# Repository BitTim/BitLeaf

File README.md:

# BitLeaf
Hardware of my Nanoleaf clone and Firmware and App to control it.

## What is where?
All the firmware code for the Arduino and Attinys can be found in the arduino folder
All the schematics and PCB designs can be found in the pcbs folder

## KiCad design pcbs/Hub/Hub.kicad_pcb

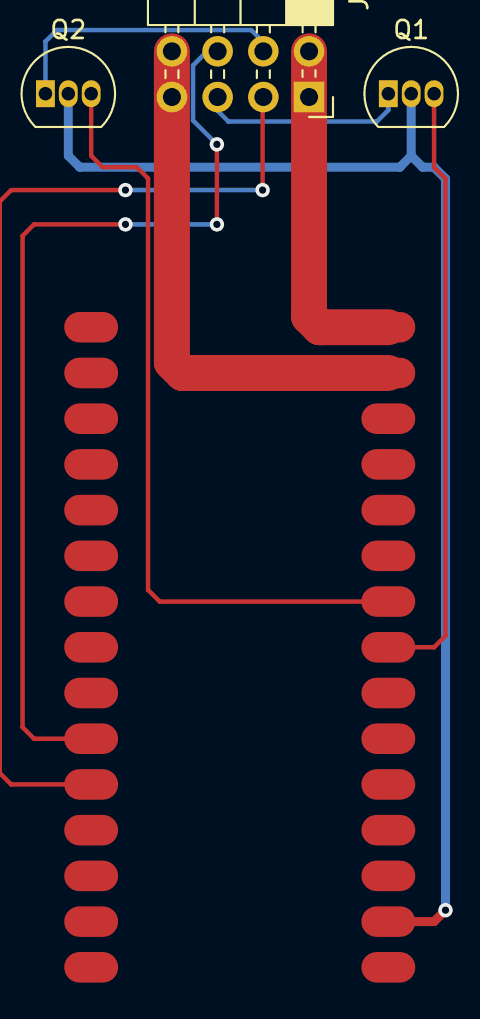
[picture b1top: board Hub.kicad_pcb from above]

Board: 2 copper layers, 4 parts (0 on the bottom side), 9 nets.

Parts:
J1: Arduino-NANO-33; NANO_33_Footprint_SMD_Castell
J2: Conn_A; PinSocket_2x04_P2.54mm_Horizontal
Q1, Q2: BS170; TO-92_Inline

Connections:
+3V3: J1.2, Q1.2 (G), Q2.2 (G)
+5V: J1.15, J2.1, J2.2
CONA: J1.26, J2.3
GND: J1.14, J2.7, J2.8
RDYA: J1.25, J2.6
SCL_3V3: J1.9, Q2.3 (S)
SCL_5V: J2.4, Q2.1 (D)
SDA_3V3: J1.8, Q1.3 (S)
SDA_5V: J2.5, Q1.1 (D)

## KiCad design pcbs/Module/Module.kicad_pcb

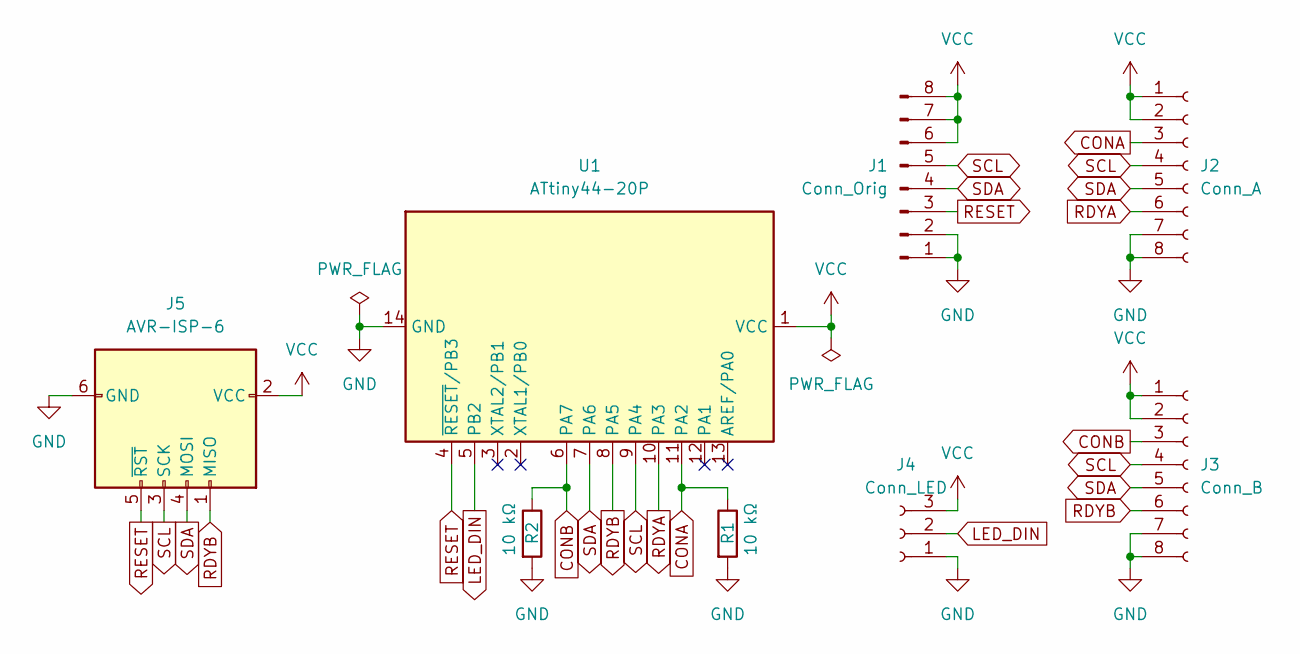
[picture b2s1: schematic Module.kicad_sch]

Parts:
J1: Conn_Orig; PinHeader_1x08_P2.54mm_Vertical
J2: Conn_A; PinSocket_2x04_P2.54mm_Horizontal
J3: Conn_B; PinSocket_2x04_P2.54mm_Horizontal
J4: Conn_LED; PinSocket_1x03_P2.54mm_Horizontal
J5: AVR-ISP-6; PinHeader_2x03_P2.54mm_Horizontal
R1, R2: 10 kΩ; R_Axial_DIN0207_L6.3mm_D2.5mm_P7.62mm_Horizontal
U1: ATtiny44-20P; DIP-14_W7.62mm_Socket

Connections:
CONA: J2.3, R1.1, U1.11 (PA2)
CONB: J3.3, R2.1, U1.6 (PA7)
GND: J1.1, J1.2, J2.7, J2.8, J3.7, J3.8, J4.1, J5.6 (GND), R1.2, R2.2, U1.14 (GND)
LED_DIN: J4.2, U1.5 (PB2)
RDYA: J2.6, U1.10 (PA3)
RDYB: J3.6, J5.1 (MISO), U1.8 (PA5)
RESET: J1.3, J5.5 (~RST), U1.4 (~RESET/PB3)
SCL: J1.5, J2.4, J3.4, J5.3 (SCK), U1.9 (PA4)
SDA: J1.4, J2.5, J3.5, J5.4 (MOSI), U1.7 (PA6)
VCC: J1.6, J1.7, J1.8, J2.1, J2.2, J3.1, J3.2, J4.3, J5.2 (VCC), U1.1 (VCC)

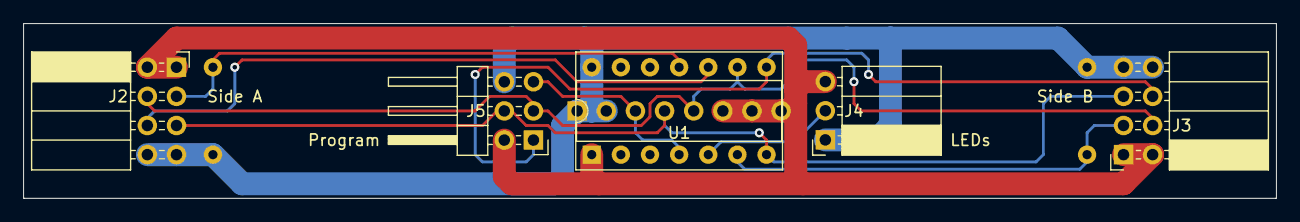
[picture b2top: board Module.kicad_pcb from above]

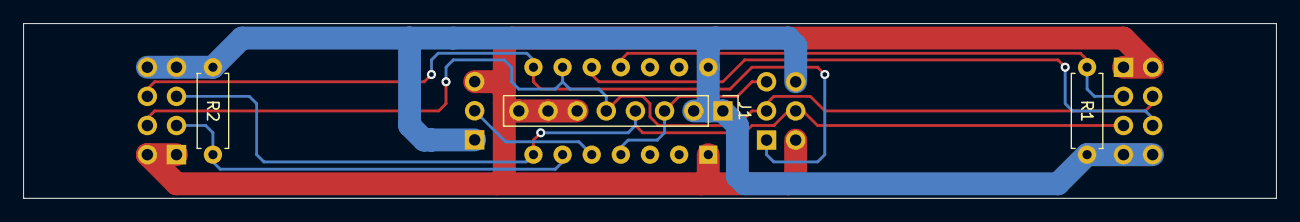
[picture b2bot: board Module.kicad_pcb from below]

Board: 2 copper layers, 109.2 x 15.2 mm, 8 parts (3 on the bottom side), 10 nets.

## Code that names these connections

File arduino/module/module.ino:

#include <Wire.h>
#include "packet.h"

#define UNASS_ADDR 0x08

#define TIMEOUT 3000

#define RDYA_PIN 4
#define RDYB_PIN 5
#define CONA_PIN 6
#define CONB_PIN 7

#define RED_LED_PIN 8
#define YELLOW_LED_PIN 9
#define GREEN_LED_PIN 10

void(* resetFunc) (void) = 0;



// ===============================
//  Variables
// ===============================

volatile byte addr = UNASS_ADDR;
volatile byte recAddr = 0;
volatile byte inBuffer[MAX_PACKET_LEN] = { 0 };

bool redOn = true;
bool greenOn = false;
bool yellowOn = false;



// ===============================
// Handlers
// ===============================

void negotiateAddress() {
  int timeout = 0;
  while(Wire.available() < 1 && timeout++ < TIMEOUT) { delay(1); }
  
  if(Wire.available() > 0) { recAddr = Wire.read(); }
}

void applyAddress()
{
  if(recAddr <= UNASS_ADDR) {
    reset();
    return;
  }

  addr = recAddr;
	Wire.end();
  
	initI2C();
  setGreenLED();
}

void onReceive() {
	// Construct packet
	int idx = 0;
  
  int timeout = 0;
  while(Wire.available() < 1 && timeout++ < TIMEOUT) { delay(1); }

	while(Wire.available() > 0) {				// Read available data into buffer
		inBuffer[idx++] = Wire.read();
    if(idx >= MAX_PACKET_LEN) break;
	}
}

void onRequest() {
	// Interpret packet (See packet.h)
	if(inBuffer[0] == Commands::sideA) checkSide(true);
	if(inBuffer[0] == Commands::sideB) checkSide(false);
	if(inBuffer[0] == Commands::reset) reset();
	if(inBuffer[0] == Commands::toggleLED) toggleYellowLED();

	memset(inBuffer, 0, MAX_PACKET_LEN);
}



// ===============================
// Functions
// ===============================

void reset()
{
  Wire.write(1);
  Wire.end();
  resetFunc();
}

void initI2C() {
  Wire.begin(addr);
  
	if(addr == UNASS_ADDR) {
		Wire.onReceive(negotiateAddress);
    Wire.onRequest(applyAddress);
	} else {
		Wire.onReceive(onReceive);
    Wire.onRequest(onRequest);
	}
}

void checkSide(bool sideA) { // if sideA is false, side B will be used
	byte connected = digitalRead(sideA ? CONA_PIN : CONB_PIN) & 0xFF;
	digitalWrite(sideA ? RDYA_PIN : RDYB_PIN, connected > 0 ? HIGH : LOW);
	Wire.write(connected);
}

void setRedLED() {
  redOn = true;
  greenOn = false;
	digitalWrite(RED_LED_PIN, HIGH);
	digitalWrite(GREEN_LED_PIN, LOW);
}

void setGreenLED() {
  redOn = false;
  greenOn = true;
	digitalWrite(RED_LED_PIN, LOW);
	digitalWrite(GREEN_LED_PIN, HIGH);
}

void toggleYellowLED() {
  digitalWrite(YELLOW_LED_PIN, yellowOn ? LOW : HIGH);
  yellowOn = !yellowOn;
}

void initPins() {
  pinMode(RED_LED_PIN, OUTPUT);  
  pinMode(YELLOW_LED_PIN, OUTPUT);
  pinMode(GREEN_LED_PIN, OUTPUT);
  
  pinMode(RDYA_PIN, OUTPUT);  
  pinMode(RDYB_PIN, OUTPUT);  
  pinMode(CONA_PIN, INPUT);  
  pinMode(CONB_PIN, INPUT);  

  digitalWrite(RDYA_PIN, LOW);
  digitalWrite(RDYB_PIN, LOW);

  digitalWrite(SDA, LOW);
  digitalWrite(SCL, LOW);
}



// ===============================
// Main Functions
// ===============================

void setup() {
	addr = UNASS_ADDR;
	initPins();
	setRedLED();
  
	initI2C();
}

void loop() {
	
}

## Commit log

2022-11-19 Fixed address protocol and added resetting of all panels on startup
2022-11-19 Added TODO
2022-11-21 Removed checking of RDYO_PIN in software
    This is now handled in hardware
2022-11-21 Shrunk module sketch to under 2KB
    Protocol seems to be more reliable as well
2022-11-23 Added hotplug support
2022-11-23 Now added discovery in loop for hotplug support
2022-11-23 Fixed hotplug support and added testing animation
2022-11-27 Added PCBs and schematics to projects
